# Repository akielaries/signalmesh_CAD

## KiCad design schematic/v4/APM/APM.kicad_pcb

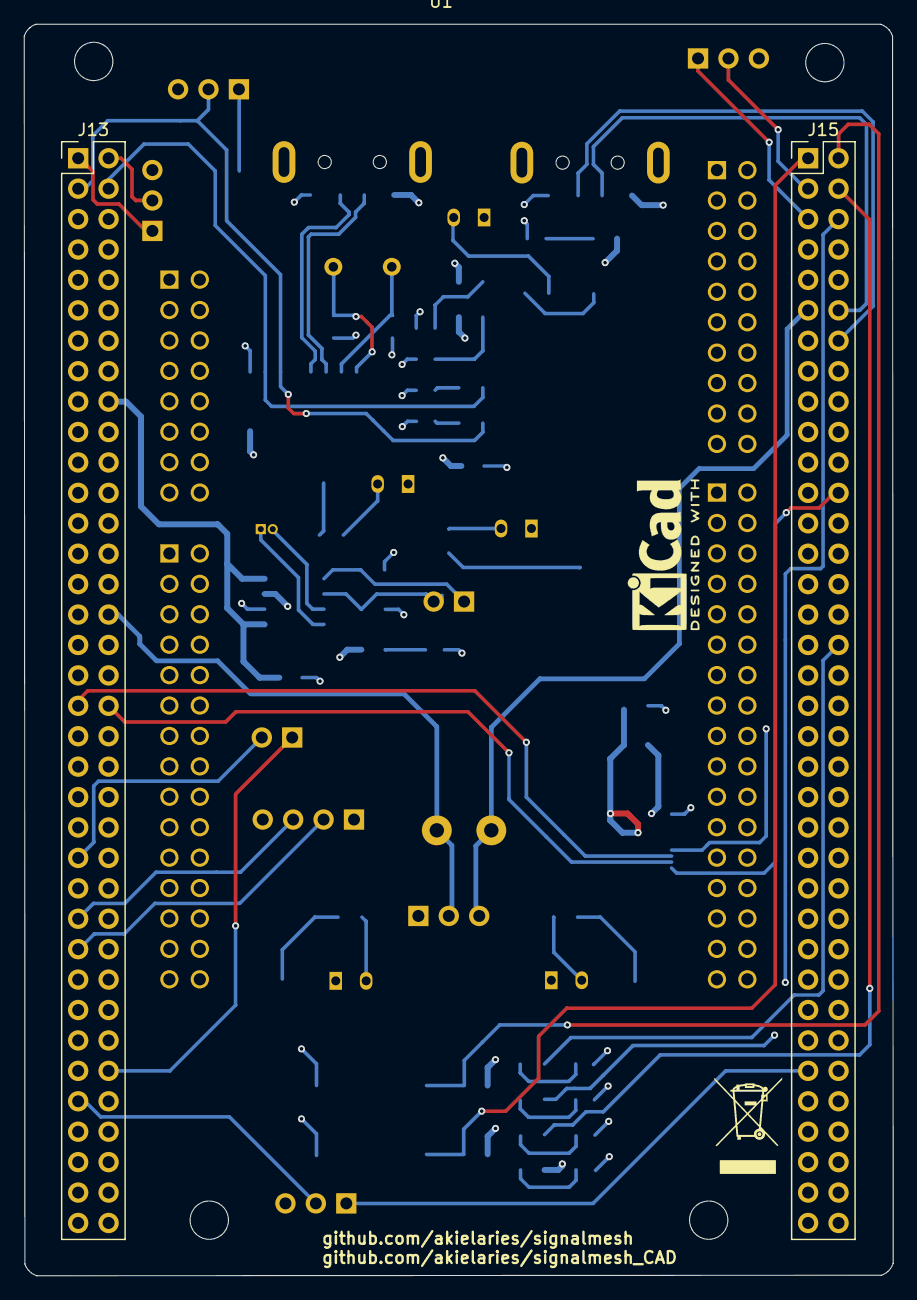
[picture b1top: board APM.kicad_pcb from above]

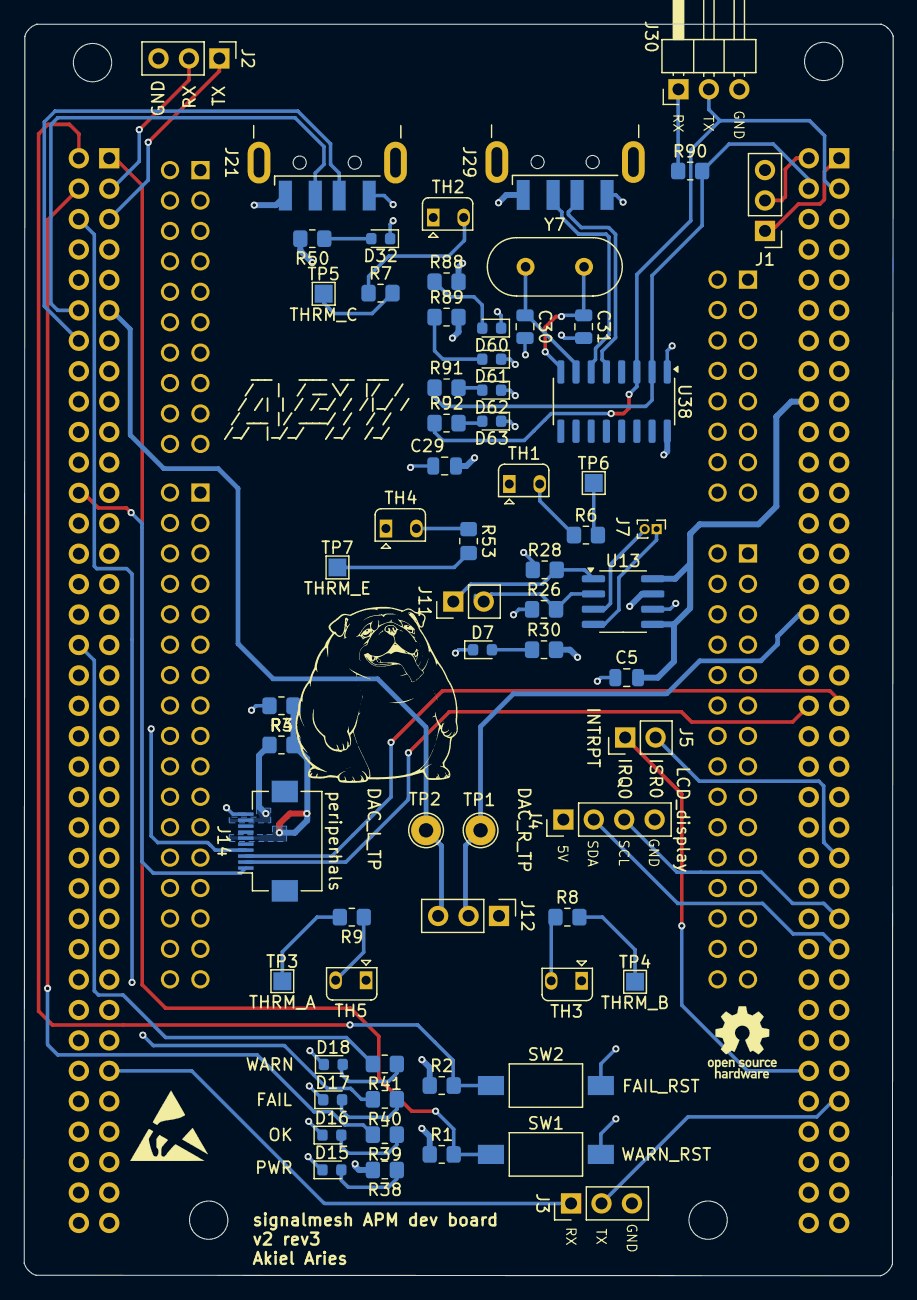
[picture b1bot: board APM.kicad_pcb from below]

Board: 4 copper layers, 72.5 x 104.5 mm, 68 parts (65 on the bottom side), 58 nets.

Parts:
C5: 0.1uf; C_0805_2012Metric
C29, C30, C31: 22pf; C_0805_2012Metric
D7, D32, D60, D61: LED_PWR; LED_0603_1608Metric
D15: PWR; LED_0603_1608Metric
D16: OK; LED_0603_1608Metric
D17: FAIL; LED_0603_1608Metric
D18: WARN; LED_0603_1608Metric
D62: TXD; LED_0603_1608Metric
D63: RXD; LED_0603_1608Metric
J1: ACM_CTRL; PinHeader_1x03_P2.54mm_Vertical
J2: CAN; PinHeader_1x03_P2.54mm_Vertical
J3: 7SDD_CTRL; PinHeader_1x03_P2.54mm_Vertical
J4: LCD_display; PinHeader_1x04_P2.54mm_Vertical
J5: INTRPT; PinHeader_1x02_P2.54mm_Vertical
J7: TDM_PMS_I2C; PinHeader_1x02_P1.00mm_Vertical
J11: INA219_CONFIG; PinHeader_1x02_P2.54mm_Vertical
J12: AUDIO_OUT; PinHeader_1x03_P2.54mm_Vertical
J13, J15: Conn_02x36_Odd_Even; PinHeader_2x36_P2.54mm_Vertical
J14: periperhals; Hirose_FH12-10S-0.5SH_1x10-1MP_P0.50mm_Horizontal
J21, J29: USB_A; USB_A_CNCTech_1001-011-01101_Horizontal
J30: UART_DEBUG; PinHeader_1x03_P2.54mm_Horizontal
R1, R2, R30, R38, R39, R40, R41, R50, R88, R89, R91, R92: 300; R_0805_2012Metric_Pad1.20x1.40mm_HandSolder
R3, R6, R7, R8, R9, R26, R28, R53: 10k; R_0805_2012Metric_Pad1.20x1.40mm_HandSolder
R4: 20k; R_0805_2012Metric_Pad1.20x1.40mm_HandSolder
R90: 1k5; R_0805_2012Metric_Pad1.20x1.40mm_HandSolder
SW1: WARN_RST; SW_SPST_FSMSM
SW2: FAIL_RST; SW_SPST_FSMSM
TH1, TH2, TH3, TH4, TH5: 10k; Heraeus_TO-92-2
TP1: DAC_R_TP; TestPoint_THTPad_D2.5mm_Drill1.2mm
TP2: DAC_L_TP; TestPoint_THTPad_D2.5mm_Drill1.2mm
TP3: THRM_A; TestPoint_Pad_1.5x1.5mm
TP4: THRM_B; TestPoint_Pad_1.5x1.5mm
TP5: THRM_C; TestPoint_Pad_1.5x1.5mm
TP6: THRM_D; TestPoint_Pad_1.5x1.5mm
TP7: THRM_E; TestPoint_Pad_1.5x1.5mm
U1: NUCLEO-H753ZI; ST_Morpho_and_Zio_Connectors_144_STLink
U13: INA219AxD; SOIC-8_3.9x4.9mm_P1.27mm
U38: CH340G; SOIC-16_3.9x9.9mm_P1.27mm
Y7: 12MHz; Crystal_HC49-4H_Vertical

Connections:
5V_APM: C29.2, J4.1, J14.9, J21.1 (VBUS), J29.1 (VBUS), R1.1, R2.1, R3.1, R30.2, R38.2, R50.2, R88.2, R89.2, U13.7 (IN-), U38.16 (VCC)
5V_APM_MCU: C5.2, J13.18, U13.5 (VS), U13.8 (IN+)
/3V3_APM: J14.6, R3.2, R4.1
/7SDD_CMD_RX: J3.2, J13.63
/7SDD_CMD_TX: J3.1, J15.61
/APM_CAN_RD: J2.2, J15.3
/APM_CAN_TD: J2.1, J15.5
/APM_CMD_RX: J1.2, J13.2
/APM_CMD_TX: J1.1, J13.1
/APM_DAC_L: J12.3, J15.11, TP2.1
/APM_DAC_R: J12.2, J13.32, TP1.1
/APM_DBG_RX: J13.4, R90.2, R91.1, U38.2 (TXD)
/APM_DBG_TX: J13.3, J30.2, R92.1, U38.3 (RXD)
/APM_FAIL_RST: J15.2, R2.2, SW2.1
/APM_I2C1_SCL: J4.3, J13.51
/APM_I2C1_SDA: J4.2, J13.53
/APM_IRQ0: J5.1, J13.62
/APM_ISR0: J5.2, J13.47
/APM_LED_FAIL: J15.34, R41.2
/APM_LED_OK: J15.4, R39.2
/APM_LED_WARN: J15.6, R40.2
/APM_USB_D+: J15.14, J21.3 (D+)
/APM_USB_D-: J15.12, J21.2 (D-)
/APM_WARN_RST: J15.1, R1.2, SW1.1
/POT_1: J14.1, J15.24
/POT_2: J13.38, J14.2
/POT_3: J13.37, J14.3
/POT_4: J14.4, J15.37
/TDM_SCL: J7.1, U13.4 (SCL)
/TDM_SDA: J7.2, U13.3 (SDA)
/THRM_A: R9.2, TP3.1
/THRM_B: R8.2, TP4.1
/THRM_C: R7.2, TP5.1
/THRM_D: R6.2, TP6.1
/THRM_E: R53.2, TP7.1
/USB_debug_APM/APM_DBG_TX: J30.1, R90.1
/USB_debug_APM/D+: J29.3 (D+), U38.5 (UD+)
/USB_debug_APM/D-: J29.2 (D-), U38.6 (UD-)
GND: C5.1, C29.1, C30.2, C31.2, D7.1 (K), D15.1 (K), D16.1 (K), D17.1 (K), D18.1 (K), D32.1 (K), D60.1 (K), D61.1 (K), D62.1 (K), D63.1 (K), J1.3, J2.3, J3.3, J4.4, J13.8, J14.10, J21.4 (GND), J29.4 (GND), J30.3, R4.2, R26.1, R28.1, SW1.2, SW2.2, TH1.1, TH2.1, TH3.1, TH4.1, TH5.1, U13.6 (GND), U38.1 (GND)
unnamed: D7.2 (A), R30.1
unnamed: D15.2 (A), R38.1
unnamed: D16.2 (A), R39.1
unnamed: D17.2 (A), R40.1
unnamed: D18.2 (A), R41.1
unnamed: D32.2 (A), R50.1
unnamed: D60.2 (A), R88.1
unnamed: D61.2 (A), R89.1
unnamed: D62.2 (A), R91.2
unnamed: D63.2 (A), R92.2
unnamed: J11.1, R28.2, U13.1 (A1)
unnamed: J11.2, R26.2, U13.2 (A0)
unnamed: R6.1, TH1.2
unnamed: R7.1, TH2.2
unnamed: R8.1, TH3.2
unnamed: R9.1, TH5.2
unnamed: R53.1, TH4.2
unnamed: C30.1, U38.7 (XI), Y7.1
unnamed: C31.1, U38.8 (XO), Y7.2

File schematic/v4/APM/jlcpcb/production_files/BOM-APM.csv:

Comment,Designator,Footprint,LCSC,Quantity
Conn_02x36_Odd_Even,J15,PinHeader_2x36_P2.54mm_Vertical,,1
Conn_02x36_Odd_Even,J13,PinHeader_2x36_P2.54mm_Vertical,,1
NUCLEO-H753ZI,U1,ST_Morpho_and_Zio_Connectors_144_STLink,,1
10k,R6,R_0805_2012Metric_Pad1.20x1.40mm_HandSolder,,1
INTRPT,J5,PinHeader_1x02_P1.00mm_Vertical,,1
10k,TH4,Heraeus_TO-92-2,,1
22pf,C30,C_0805_2012Metric,,1
PWR,D15,LED_0603_1608Metric,,1
ACM_CTRL,J1,PinHeader_1x03_P1.00mm_Vertical,,1
300,R92,R_0805_2012Metric_Pad1.20x1.40mm_HandSolder,,1
LCD_display,J4,PinHeader_1x04_P1.00mm_Vertical,,1
10k,TH5,Heraeus_TO-92-2,,1
THRM_E,TP7,TestPoint_Pad_1.5x1.5mm,,1
LED_PWR,D60,LED_0603_1608Metric,,1
CAN,J2,PinHeader_1x03_P1.00mm_Vertical,,1
300,R1,R_0805_2012Metric_Pad1.20x1.40mm_HandSolder,,1
10k,R8,R_0805_2012Metric_Pad1.20x1.40mm_HandSolder,,1
RXD,D63,LED_0603_1608Metric,,1
FAIL,D17,LED_0603_1608Metric,,1
THRM_B,TP4,TestPoint_Pad_1.5x1.5mm,,1
THRM_A,TP3,TestPoint_Pad_1.5x1.5mm,,1
OK,D16,LED_0603_1608Metric,,1
7SDD_CTRL,J3,PinHeader_1x03_P1.00mm_Vertical,,1
INA219AxD,U13,SOIC-8_3.9x4.9mm_P1.27mm,,1
CH340G,U38,SOIC-16_3.9x9.9mm_P1.27mm,,1
TDM_PMS_I2C,J7,PinHeader_1x02_P1.00mm_Vertical,,1
TXD,D62,LED_0603_1608Metric,,1
300,R88,R_0805_2012Metric_Pad1.20x1.40mm_HandSolder,,1
10k,TH3,Heraeus_TO-92-2,,1
10k,R28,R_0805_2012Metric_Pad1.20x1.40mm_HandSolder,,1
300,R2,R_0805_2012Metric_Pad1.20x1.40mm_HandSolder,,1
USB_A,J21,USB_A_CNCTech_1001-011-01101_Horizontal,,1
10k,R7,R_0805_2012Metric_Pad1.20x1.40mm_HandSolder,,1
300,R30,R_0805_2012Metric_Pad1.20x1.40mm_HandSolder,,1
22pf,C31,C_0805_2012Metric,,1
AUDIO_OUT,J12,NS-Tech_Grove_1x04_P2mm_Vertical,,1
10k,R26,R_0805_2012Metric_Pad1.20x1.40mm_HandSolder,,1
300,R41,R_0805_2012Metric_Pad1.20x1.40mm_HandSolder,,1
300,R38,R_0805_2012Metric_Pad1.20x1.40mm_HandSolder,,1
300,R40,R_0805_2012Metric_Pad1.20x1.40mm_HandSolder,,1
300,R39,R_0805_2012Metric_Pad1.20x1.40mm_HandSolder,,1
LED_PWR,D7,LED_0603_1608Metric,,1
FAIL_RST,SW1,SW_SPST_FSMSM,,1
10k,TH1,Heraeus_TO-92-2,,1
INA219_CONFIG,J11,PinHeader_1x02_P1.27mm_Vertical,,1
10k,TH2,Heraeus_TO-92-2,,1
300,R89,R_0805_2012Metric_Pad1.20x1.40mm_HandSolder,,1
0.1uf,C5,C_0805_2012Metric,,1
DAC_R_TP,TP1,TestPoint_THTPad_D2.5mm_Drill1.2mm,,1
DAC_L_TP,TP2,TestPoint_THTPad_D2.5mm_Drill1.2mm,,1
22pf,C29,C_0805_2012Metric,,1
FAIL_RST,SW2,SW_SPST_FSMSM,,1
1k5,R90,R_0805_2012Metric_Pad1.20x1.40mm_HandSolder,,1
THRM_D,TP6,TestPoint_Pad_1.5x1.5mm,,1
LED_PWR,D32,LED_0603_1608Metric,,1
LED_PWR,D61,LED_0603_1608Metric,,1
10k,R53,R_0805_2012Metric_Pad1.20x1.40mm_HandSolder,,1
300,R50,R_0805_2012Metric_Pad1.20x1.40mm_HandSolder,,1
USB_A,J29,USB_A_CNCTech_1001-011-01101_Horizontal,,1
300,R91,R_0805_2012Metric_Pad1.20x1.40mm_HandSolder,,1
WARN,D18,LED_0603_1608Metric,,1
THRM_C,TP5,TestPoint_Pad_1.5x1.5mm,,1
12MHz,Y7,Crystal_HC49-4H_Vertical,,1
10k,R9,R_0805_2012Metric_Pad1.20x1.40mm_HandSolder,,1
UART_DEBUG,J30,PinHeader_1x03_P1.00mm_Horizontal,,1

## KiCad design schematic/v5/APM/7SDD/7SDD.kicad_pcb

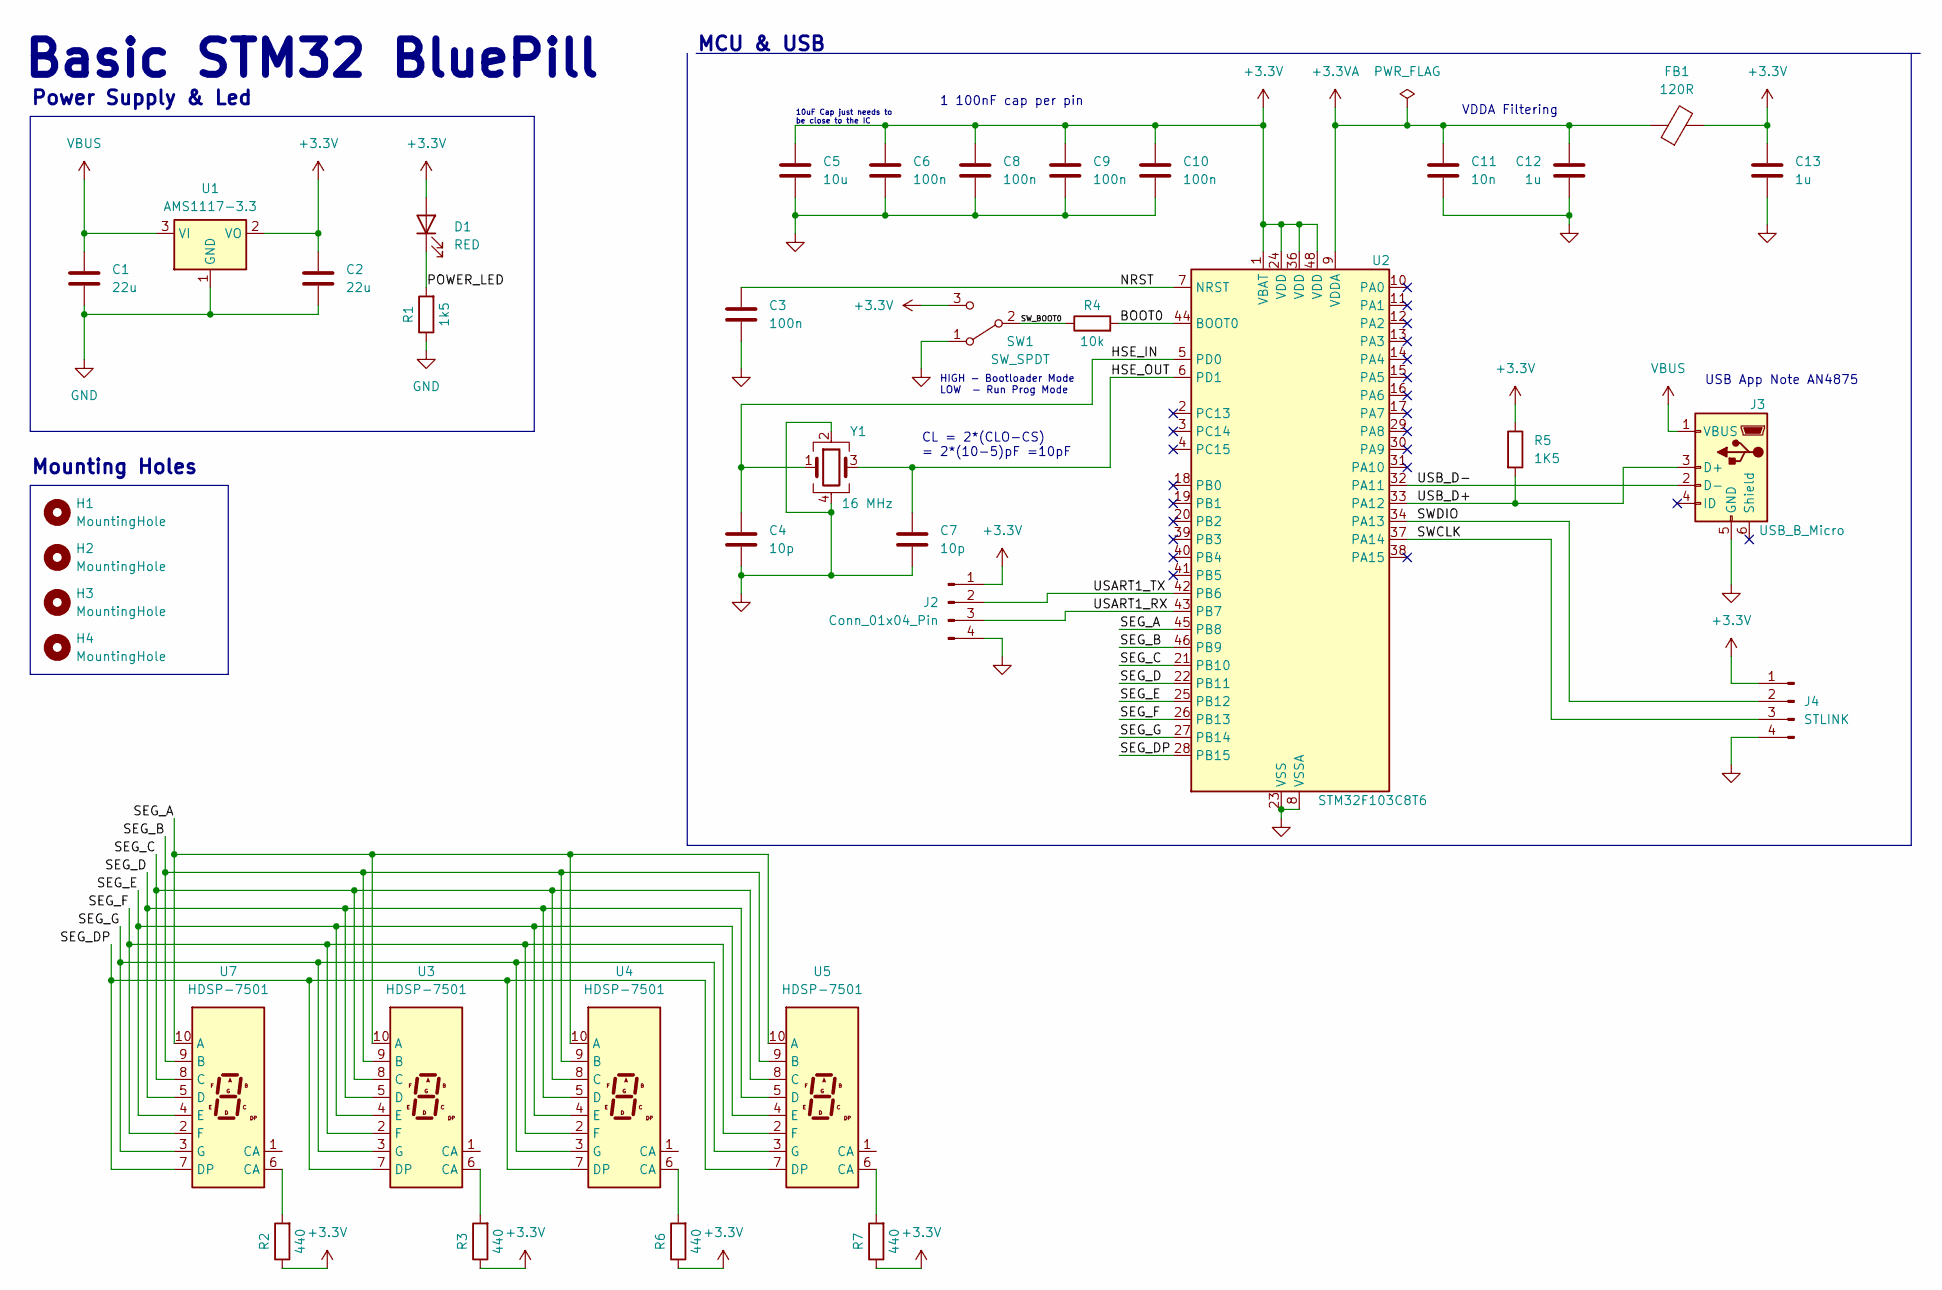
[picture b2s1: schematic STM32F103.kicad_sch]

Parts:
C1, C2: 22u; C_0805_2012Metric
C3, C6, C8, C9, C10: 100n; C_0402_1005Metric
C4, C7: 10p; C_0402_1005Metric
C5: 10u; C_0603_1608Metric
C11: 10n; C_0402_1005Metric
C12, C13: 1u; C_0402_1005Metric
D1: RED; LED_0603_1608Metric
FB1: 120R; L_0603_1608Metric
H1, H2, H3, H4: MountingHole; MountingHole_2.2mm_M2
J2: Conn_01x04_Pin; PinHeader_1x04_P2.54mm_Vertical
J3: USB_B_Micro; USB_Micro-B_Wuerth_629105150521
J4: STLINK; PinHeader_1x04_P2.54mm_Vertical
R1: 1k5; R_0402_1005Metric
R2, R3, R6, R7: 440; R_0402_1005Metric
R4: 10k; R_0402_1005Metric
R5: 1K5; R_0402_1005Metric
SW1: SW_SPDT; SW_SPDT_PCM12
U1: AMS1117-3.3; SOT-223-3_TabPin2
U2: STM32F103C8T6; LQFP-48_7x7mm_P0.5mm
U3, U4, U5, U7: HDSP-7501; HDSP-A151
Y1: 16 MHz; Crystal_SMD_3225-4Pin_3.2x2.5mm

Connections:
+3.3V: C2.1, C5.1, C6.1, C8.1, C9.1, C10.1, C13.1, D1.2 (A), FB1.2, J2.1, J4.1, R2.1, R3.1, R5.1, R6.1, R7.1, SW1.3 (C), U1.2 (VO), U2.1 (VBAT), U2.24 (VDD), U2.36 (VDD), U2.48 (VDD)
+3.3VA: C11.1, C12.1, FB1.1, U2.9 (VDDA)
/STM32F103/BOOT0: R4.2, U2.44 (BOOT0)
/STM32F103/HSE_IN: C4.1, U2.5 (PD0), Y1.1
/STM32F103/HSE_OUT: C7.1, U2.6 (PD1), Y1.3
/STM32F103/NRST: C3.1, U2.7 (NRST)
/STM32F103/POWER_LED: D1.1 (K), R1.2
/STM32F103/SEG_A: U2.45 (PB8), U3.10 (A), U4.10 (A), U5.10 (A), U7.10 (A)
/STM32F103/SEG_B: U2.46 (PB9), U3.9 (B), U4.9 (B), U5.9 (B), U7.9 (B)
/STM32F103/SEG_C: U2.21 (PB10), U3.8 (C), U4.8 (C), U5.8 (C), U7.8 (C)
/STM32F103/SEG_D: U2.22 (PB11), U3.5 (D), U4.5 (D), U5.5 (D), U7.5 (D)
/STM32F103/SEG_DP: U2.28 (PB15), U3.7 (DP), U4.7 (DP), U5.7 (DP), U7.7 (DP)
/STM32F103/SEG_E: U2.25 (PB12), U3.4 (E), U4.4 (E), U5.4 (E), U7.4 (E)
/STM32F103/SEG_F: U2.26 (PB13), U3.2 (F), U4.2 (F), U5.2 (F), U7.2 (F)
/STM32F103/SEG_G: U2.27 (PB14), U3.3 (G), U4.3 (G), U5.3 (G), U7.3 (G)
/STM32F103/SWCLK: J4.3, U2.37 (PA14)
/STM32F103/SWDIO: J4.2, U2.34 (PA13)
/STM32F103/SW_BOOT0: R4.1, SW1.2 (B)
/STM32F103/USART1_RX: J2.3, U2.43 (PB7)
/STM32F103/USART1_TX: J2.2, U2.42 (PB6)
/STM32F103/USB_D+: J3.3 (D+), R5.2, U2.33 (PA12)
/STM32F103/USB_D-: J3.2 (D-), U2.32 (PA11)
GND: C1.2, C2.2, C3.2, C4.2, C5.2, C6.2, C7.2, C8.2, C9.2, C10.2, C11.2, C12.2, C13.2, J2.4, J3.5 (GND), J4.4, R1.1, SW1.1 (A), U1.1 (GND), U2.8 (VSSA), U2.23 (VSS), U2.35 (VSS), U2.47 (VSS), Y1.2, Y1.4
unnamed: R2.2, U7.6 (CA)
unnamed: R3.2, U3.6 (CA)
unnamed: R6.2, U4.6 (CA)
unnamed: R7.2, U5.6 (CA)
VBUS: C1.1, J3.1 (VBUS), U1.3 (VI)

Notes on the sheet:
Mounting Holes
10uF Cap just needs to be close to the IC
USB App Note AN4875
MCU & USB
VDDA Filtering
CL = 2*(CLO-CS) = 2*(10-5)pF =10pF
HIGH - Bootloader Mode LOW - Run Prog Mode
Power Supply & Led
1 100nF cap per pin
Basic STM32 BluePill

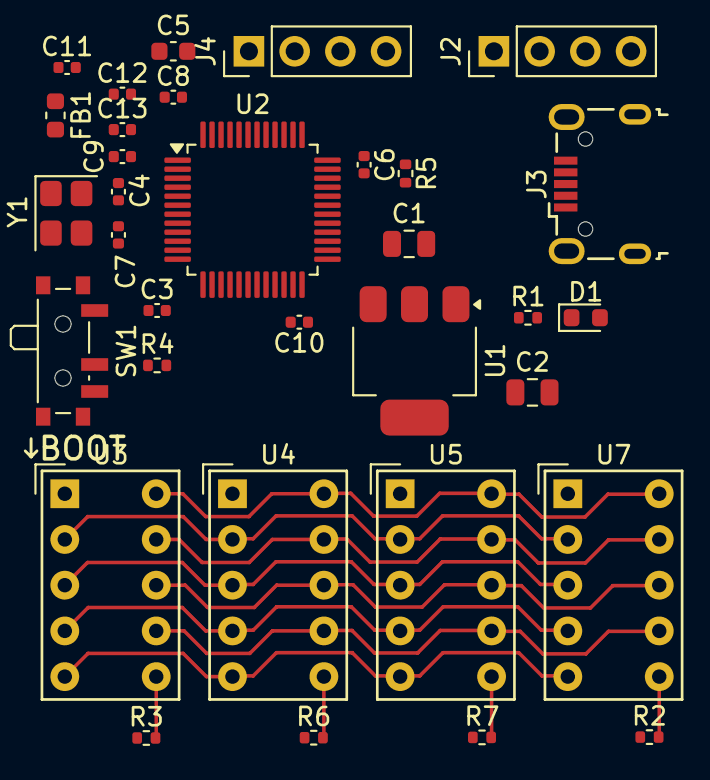
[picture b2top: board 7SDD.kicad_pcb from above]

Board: 2 copper layers, 37 parts (0 on the bottom side), 28 nets.
